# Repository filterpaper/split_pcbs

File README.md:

# Open Source Split PCBs

Personal repository of modified opensource split keyboards

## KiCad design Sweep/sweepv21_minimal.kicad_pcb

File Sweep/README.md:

# Modified Sweep PCBs

Minimal [Sweepv2.1](https://github.com/davidphilipbarr/Sweep/tree/main/Sweepv2) and [Half-swept](https://github.com/davidphilipbarr/Sweep/tree/main/Sweep-half-swept) are modified with the following changes:
* Removed mascot, puck and battery support
* Removed reset switch on half-swept
* Corrected MCU pin labels and alignment
* Added switch silkscreen from Pierre's [Ferris v0.1](https://github.com/pierrechevalier83/ferris/tree/main/0.1)

Custom [Sweepv2](https://github.com/davidphilipbarr/Sweep/tree/main/Sweepv2) are modified with the following changes:
* Removed mascot, puck and battery support
* Corrected MCU pin lables and alignment

## How To Build
See David Barr's [Sweep](https://github.com/davidphilipbarr/Sweep) page for instructions.

## Designed By
* [Pierre Chevalier](https://github.com/pierrechevalier83/ferris/)
* [David Barr](https://github.com/davidphilipbarr/Sweep/)
* [Ibnu Daru Aji](https://github.com/ibnuda/)

## Renders

### Sweepv2.1

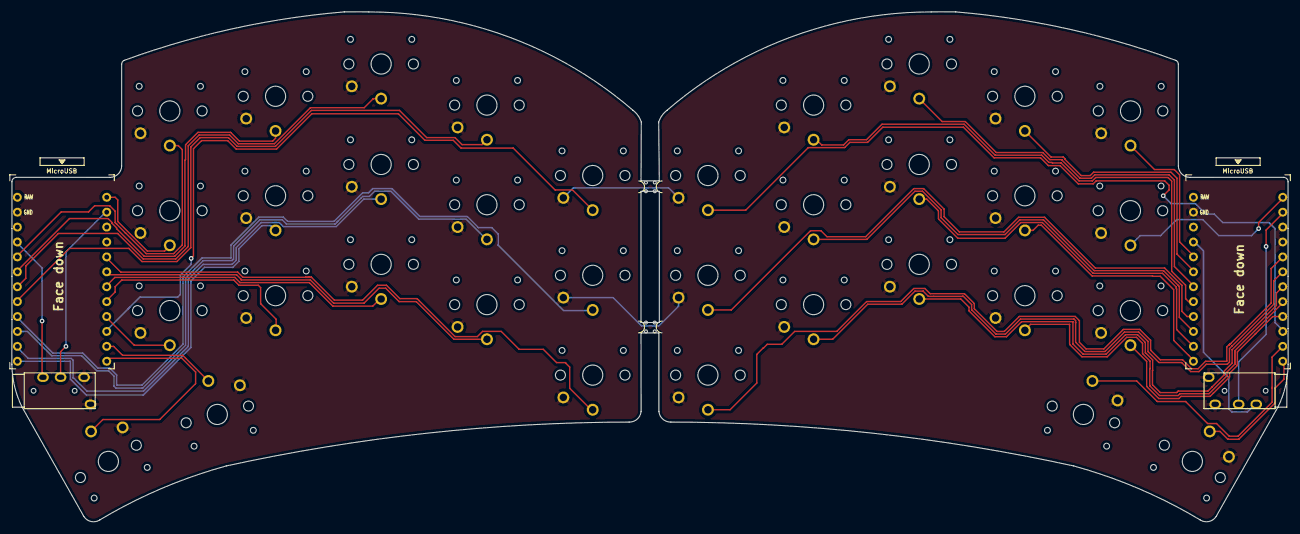
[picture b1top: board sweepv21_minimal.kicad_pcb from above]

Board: 2 copper layers, 217.4 x 86.9 mm, 40 parts (0 on the bottom side), 39 nets.

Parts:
J1, J2: AudioJack4dpb; TRRS-PJ-320A
SW2, SW2_r1, SW3, SW3_r1, SW4, SW4_r1, SW5, SW5_r1, SW6, SW6_r1, SW7_r1, SW8, SW8_r1, SW9, SW9_r1, SW11, SW11_r1, SW12, SW12_r1, SW13_r1, SW14, SW15, SW15_r1, SW16, SW16_r1, SW17, SW17_r1, SW18, SW18_r1, SW20, SW20_r1, SW21, SW21_r1: SW_Push; SW_PG1350_nonrev_DPB
SW10: SW_Push; SW_PG1350_rev_DPB
U1, U2: ProMicro-kbd; ProMicro_v3_min
mouse-bite-2mm-slot, mouse-bite-2mm-slot#2: VAL**; mouse-bite-2mm-slot-with-space-for-track

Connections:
Switch1: SW2.1, U1.10
Switch1_r: SW2_r1.1, U2.10
Switch2: SW3.1, U1.17
Switch2_r: SW3_r1.1, U2.17
Switch3: SW4.1, U1.18
Switch3_r: SW4_r1.1, U2.18
Switch4: SW5.1, U1.19
Switch4_r: SW5_r1.1, U2.19
Switch5: SW6.1, U1.20
Switch5_r: SW6_r1.1, U2.20
Switch6: SW8.1, U1.16
Switch6_r: SW7_r1.1, U2.16
Switch7: SW9.1, U1.15
Switch7_r: SW8_r1.1, U2.15
Switch8: SW10.1, U1.14
Switch8_r: SW9_r1.1, U2.14
Switch9: SW11.1, U1.13
Switch9_r: SW11_r1.1, U2.13
Switch10: SW12.1, U1.1
Switch10_r: SW12_r1.1, U2.1
Switch11: SW14.1, U1.5
Switch11_r: SW13_r1.1, U2.5
Switch12: SW15.1, U1.6
Switch12_r: SW18_r1.1, U2.6
Switch13: SW16.1, U1.7
Switch13_r: SW15_r1.1, U2.7
Switch14: SW17.1, U1.8
Switch14_r: SW16_r1.1, U2.8
Switch15: SW18.1, U1.9
Switch15_r: SW17_r1.1, U2.9
Switch16: SW21.1, U1.11
Switch16_r: SW21_r1.1, U2.11
Switch17: SW20.1, U1.12
Switch17_r: SW20_r1.1, U2.12
Switch18: J2.R1, U1.2
Switch18_r: J1.R1, U2.2
gnd: J1.S, J1.T, J2.S, J2.T, SW2.2, SW2_r1.2, SW3.2, SW3_r1.2, SW4.2, SW4_r1.2, SW5.2, SW5_r1.2, SW6.2, SW6_r1.2, SW7_r1.2, SW8.2, SW8_r1.2, SW9.2, SW9_r1.2, SW10.2, SW11.2, SW11_r1.2, SW12.2, SW12_r1.2, SW13_r1.2, SW14.2, SW15.2, SW15_r1.2, SW16.2, SW16_r1.2, SW17.2, SW17_r1.2, SW18.2, SW18_r1.2, SW20.2, SW20_r1.2, SW21.2, SW21_r1.2, U1.3, U1.4, U1.23, U2.3, U2.4, U2.23
raw: U1.24, U2.24
vcc: J1.R2, J2.R2, U1.21, U2.21

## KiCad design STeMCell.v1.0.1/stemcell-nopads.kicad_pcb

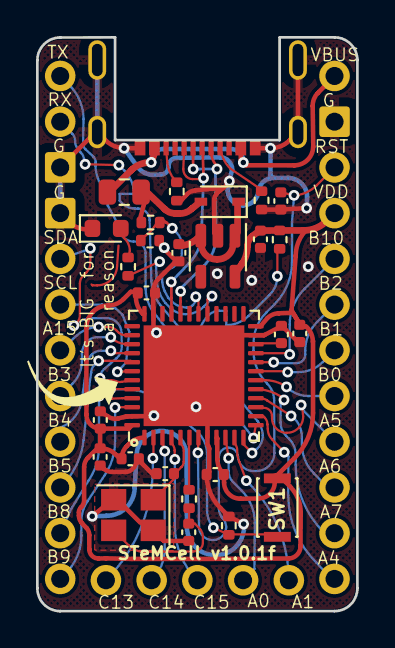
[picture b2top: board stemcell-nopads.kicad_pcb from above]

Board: 2 copper layers, 17.8 x 31.9 mm, 31 parts (0 on the bottom side), 37 nets.

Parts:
C1: 10u; C_0402_1005Metric
C2, C3, C9: 4.7u; C_0402_1005Metric
C4, C5, C6, C7, C8, C12: 100n; C_0402_1005Metric
C10, C11: 20p; C_0402_1005Metric
D1: LED; LED_0603_1608Metric
D2: 1N5819; D_SOD-323
F1: 500mA Fuse; Fuse_0805_2012Metric
J1: USB C Connector; USB-C-C168688
J2: Left; Pins12
J3: Right; Pins12
J4: Down; Pins5
R1: 220; R_0402_1005Metric
R2, R3: 5k1; R_0402_1005Metric
R4: 2k2; R_0402_1005Metric
R5: 4.7k; R_0402_1005Metric
R6, R7, R8: 10k; R_0402_1005Metric
SW1: Boot0; SW_SPST_CK_KXT3
U1: STM32F4x1CxUx; QFN-48-1EP_7x7mm_P0.5mm_EP5.6x5.6mm
U2: XC6220B331MR; SOT-23-5
Y1: HSE1 8Mhz 12pF; Crystal_SMD_3225-4Pin_3.2x2.5mm

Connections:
/BOOT0: R8.1, SW1.1 (A), U1.44 (BOOT0)
/CC1: J1.A5 (CC1), R2.1
/CC2: J1.B5 (CC2), R3.1
/HSE_IN: C10.1, U1.5 (PH0), Y1.1
/HSE_OUT: R1.2, U1.6 (PH1)
/HSE_OUT_1: C11.1, R1.1, Y1.3
/LED_R: D1.2 (A), R4.2
/NRST: C12.1, J3.3, U1.7 (NRST)
/PA0: J4.4, U1.10 (PA0)
/PA1: J4.5, U1.11 (PA1)
/PA4: J3.12, U1.14 (PA4)
/PA5: J3.9, U1.15 (PA5)
/PA6: J3.10, U1.16 (PA6)
/PA7: J3.11, U1.17 (PA7)
/PA8: R4.1, U1.29 (PA8)
/PA9: R5.2, R6.1, U1.30 (PA9)
/PA15: J2.7, U1.38 (PA15)
/PB0: J3.8, U1.18 (PB0)
/PB1: J3.7, U1.19 (PB1)
/PB2: J3.6, U1.20 (PB2)
/PB3: J2.8, U1.39 (PB3)
/PB4: J2.9, U1.40 (PB4)
/PB5: J2.10, U1.41 (PB5)
/PB8: J2.11, U1.45 (PB8)
/PB9: J2.12, U1.46 (PB9)
/PB10: J3.5, U1.21 (PB10)
/PC13: J4.1, U1.2 (PC13)
/PC14: J4.2, U1.3 (PC14)
/PC15: J4.3, U1.4 (PC15)
/USB_DN: J1.A7 (D-), J1.B7 (D-), U1.32 (PA11)
/USB_DP: J1.A6 (D+), J1.B6 (D+), U1.33 (PA12)
/VBUS_F: D2.2 (A), F1.2, R5.1
/VBUS_FF: C1.1, D2.1 (K), U2.1 (VIN), U2.3 (CE)
/VCAP1: C3.2, U1.22 (VCAP1)
GND: C1.2, C2.2, C3.1, C4.2, C5.2, C6.2, C7.2, C8.2, C9.2, C10.2, C11.2, C12.2, D1.1 (K), J1.A1 (GND), J1.S1 (SHIELD), J2.3, J2.4, J3.2, R2.2, R3.2, R6.2, R8.2, U1.8 (VSSA), U1.23 (VSS), U1.35 (VSS), U1.47 (VSS), U1.49 (VSS), U2.2 (GND), Y1.2, Y1.4
VBUS: F1.1, J1.A4 (VBUS), J3.1
VDD: C2.1, C4.1, C5.1, C6.1, C7.1, C8.1, C9.1, J3.4, R7.1, SW1.2 (B), U1.1 (VBAT), U1.9 (VDDA), U1.24 (VDD), U1.36 (VDD), U1.48 (VDD), U2.5 (VOUT)

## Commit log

2021-09-20 Add custom kicad files and gerber
2021-09-20 Rename gerber file
2021-09-20 Crop image
2021-09-20 Add custom half-swept PCB
2021-09-20 Update title
2021-09-20 Add silkscreen switch picture to half-swept
2021-09-20 Add half swept boards with silkscreen
2021-09-20 Crop front and back images
2021-09-20 Remove battery pads and overlapping silkscreen
2021-09-20 Remove reset switch
2021-09-20 Remove battery pads
2021-09-20 Align silk screen labels below MCU
2021-09-20 Add missing GND label
2021-09-20 Remove bak file
2021-09-20 Generate gerber zip
2021-09-20 Update README with detailed changes
2021-09-20 Update images
2021-09-20 Add license file from Pierre
2021-09-20 Regenerate Sweepv2 gerber
2021-09-20 Remove switch labels
2021-09-20 Remove unused power switch traces
2021-09-20 Title edit
2021-09-20 Align B2 and B6 silk label
2021-09-21 Move silk labels to bottom of MCU
2021-09-21 Remove TRRS text
2021-09-21 Align front and back switch silkscreen
2021-09-21 Align left and right switch silkscreen image
2021-09-21 Regenerate half-swept images
2021-09-21 Add more README details
2021-09-21 Update section titles
2021-09-21 Update Sweepv2 render
2021-09-21 Use minimalist file names
2021-09-21 Add Sweepv2 with puck removed
2021-09-22 Add description for custom Sweepv2
2021-09-22 Remove incorrect Sweepv2 silk bottom, add custom architeuthis.dux
2021-09-22 Replace Architeuthis.dux with no puck version
2021-09-22 Really adding architeuthis_dux_nopuck.kicad_pcb this time
2021-09-22 Move Architeuthis dux to own folder, remove hotswap sockets
2021-09-22 Update gerber path
2021-09-22 Add Architeuthis dux image
2021-09-22 Add hypergarlic with puck, battery support, and bottom silk removed
2021-09-22 Organise files into folders
2021-09-22 Add READMEs
2021-09-23 Add some renders
2021-09-23 Flip rear logo to align orientation with front
2021-09-23 Use pro micro pin labels for A.dux
2021-09-24 No logo version of Architeuthis, move silkscreens to the back of hypergarlic
2021-09-26 Keep half-swept in own folder
2021-09-26 Add Sweepv2.1 custom
2021-09-27 Remove hotswap traces and add a blank PCB version
2021-09-28 Add wireless hypergolic V1.2 bm
2021-09-28 Add images for hypergolic 1.2bm
2021-09-28 Corrected name
2021-09-28 Update image
2021-09-28 Add blank Architeuthis
2021-09-29 Add gerbers
2021-09-29 Add blank Architeuthis dux gerber
2021-09-29 Update silkscreen, add image
2021-09-29 Add BOM and build instructions
2021-09-29 Add additional build instructions
2021-09-29 Add build instructions
2021-09-29 Add links to build parts
2021-09-29 Add battery
2021-09-29 Update build instructions with links
2021-09-30 Add BOM list for MCU sockets
2021-09-30 Add list of optional socket components
2021-10-01 Remove phantom drill holes
2021-10-01 Add additional MCU controller links
2021-10-01 Add single sided clove
2021-10-04 Corrected traces and removed extra switch drill holes
2021-10-05 Archive old PCB, update circuits
2021-10-06 Add hypergolic gerbers
2021-10-07 Minor trace changes
2021-10-08 More trace corrections
2021-10-14 Add GND filled version
2021-10-21 Add hypergolic half
2021-10-25 Update garlic, add flip image
2021-10-25 Add silkscreen to hypergolic
2021-10-26 Swap silkscreen, add gerbers
2021-10-27 Update new gerbers and image
2021-10-27 Update Sweep minimal and hypergolic gerbers
2021-10-27 Add silkscreens
2021-10-28 Add LP macro3 PCB
2021-10-28 Remove gerber directory
2021-10-28 Add image and gerber
2021-10-29 Remove encoder silk
2021-11-06 Remove clove, add silkscreen image
2021-11-08 Update kicad
2021-11-08 Add gerber zip
2021-11-10 Add Paroxysm and update hypergarlic gerber
2021-11-11 Update kicad and gerber
2021-11-11 Add Elecrow specific gerber
2021-11-15 Add original and one sided copies of paroxysm
2021-11-15 Remove paroxysm oneside, simplified paroxysm_left
2021-11-15 Simplified paroxysm_right, update README
2021-11-15 Use Cradio firmware, remove Ferris name
2021-11-15 Add paroxysm render
2021-11-15 Add filled image
2021-11-17 Add readme for half-swept
2021-11-17 Add gerber
2021-11-19 Add Sweep34
2021-11-19 Add gerber file
2021-11-19 Update paroxysm
2021-11-20 Remove trace, update image
2021-12-04 Add modified Sweep High
2021-12-04 Updated TRRS to one side only
2021-12-04 Add Ferris silk versions
2021-12-05 Add combo silk version and gerber
2021-12-13 Add compatible gerber
2022-01-01 Remove Sweep34
2022-01-07 Add hypergolic high
2022-01-24 Remove half-swept
2022-02-03 Add modified left and right only paroxysm
2022-02-23 Update and corrected traces
2022-03-10 Add stemcell
2022-03-23 Add coffee stain silk
2022-04-01 Add paroxysm silk
2022-04-11 Add silk svg
2022-05-27 Update Sweep High gerber and geist grid silk
2022-06-02 Add shater PCB, update gerbers
2022-08-25 Add splinter pcb
